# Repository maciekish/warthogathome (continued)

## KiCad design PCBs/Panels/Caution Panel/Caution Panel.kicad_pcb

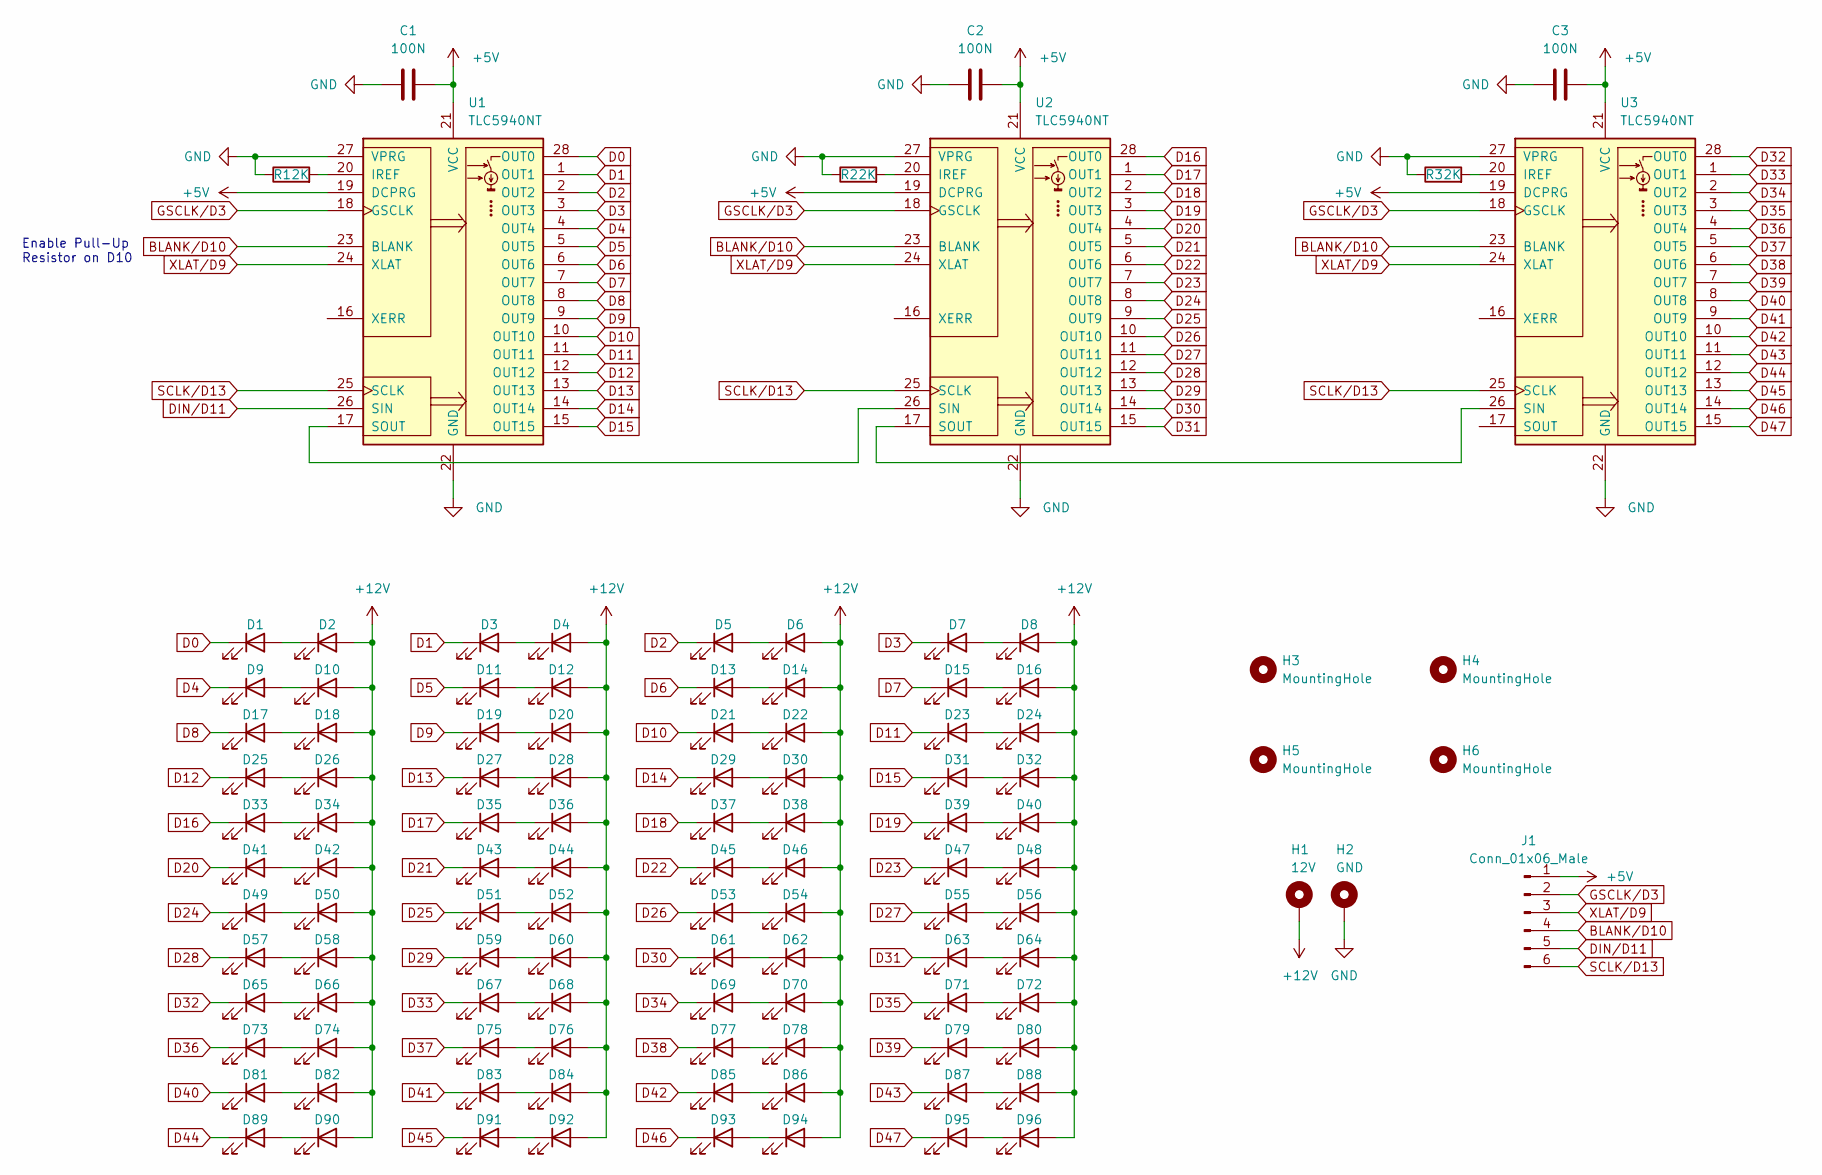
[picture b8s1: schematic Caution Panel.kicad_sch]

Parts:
C1, C2, C3: 100N; C_0805_2012Metric_Pad1.18x1.45mm_HandSolder
D1, D2, D3, D4, D5, D6, D7, D8, D9, D10, D11, D12, D13, D14, D15, D16, D17, D18, D19, D20, D21, D22, D23, D24, D25, D26, D27, D28, D29, D30, D31, D32, D33, D34, D35, D36, D37, D38, D39, D40, D41, D42, D43, D44, D45, D46, D47, D48, D49, D50, D51, D52, D53, D54, D55, D56, D57, D58, D59, D60, D61, D62, D63, D64, D65, D66, D67, D68, D69, D70, D71, D72, D73, D74, D75, D76, D77, D78, D79, D80, D81, D82, D83, D84, D85, D86, D87, D88, D89, D90, D91, D92, D93, D94, D95, D96: GREEN; LED_2010_5025Metric_Pad1.52x2.65mm_HandSolder
H1: 12V; MountingHole_2.2mm_M2_Pad
H2: GND; MountingHole_2.2mm_M2_Pad
H3, H4, H5, H6: MountingHole; MountingHole_4mm
J1: Conn_01x06_Male; PinHeader_1x06_P2.54mm_Vertical
R1, R2, R3: 2K; R_1210_3225Metric_Pad1.30x2.65mm_HandSolder
U1, U2, U3: TLC5940NT; DIP-28_W7.62mm

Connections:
+5V: C1.2, C2.2, C3.2, J1.1, U1.19 (DCPRG), U1.21 (VCC), U2.19 (DCPRG), U2.21 (VCC), U3.19 (DCPRG), U3.21 (VCC)
+12V: D2.2 (A), D4.2 (A), D6.2 (A), D8.2 (A), D10.2 (A), D12.2 (A), D14.2 (A), D16.2 (A), D18.2 (A), D20.2 (A), D22.2 (A), D24.2 (A), D26.2 (A), D28.2 (A), D30.2 (A), D32.2 (A), D34.2 (A), D36.2 (A), D38.2 (A), D40.2 (A), D42.2 (A), D44.2 (A), D46.2 (A), D48.2 (A), D50.2 (A), D52.2 (A), D54.2 (A), D56.2 (A), D58.2 (A), D60.2 (A), D62.2 (A), D64.2 (A), D66.2 (A), D68.2 (A), D70.2 (A), D72.2 (A), D74.2 (A), D76.2 (A), D78.2 (A), D80.2 (A), D82.2 (A), D84.2 (A), D86.2 (A), D88.2 (A), D90.2 (A), D92.2 (A), D94.2 (A), D96.2 (A), H1.1
BLANK/D10: J1.4, U1.23 (BLANK), U2.23 (BLANK), U3.23 (BLANK)
D0: D1.1 (K), U1.28 (OUT0)
D1: D3.1 (K), U1.1 (OUT1)
D2: D5.1 (K), U1.2 (OUT2)
D3: D7.1 (K), U1.3 (OUT3)
D4: D9.1 (K), U1.4 (OUT4)
D5: D11.1 (K), U1.5 (OUT5)
D6: D13.1 (K), U1.6 (OUT6)
D7: D15.1 (K), U1.7 (OUT7)
D8: D17.1 (K), U1.8 (OUT8)
D9: D19.1 (K), U1.9 (OUT9)
D10: D21.1 (K), U1.10 (OUT10)
D11: D23.1 (K), U1.11 (OUT11)
D12: D25.1 (K), U1.12 (OUT12)
D13: D27.1 (K), U1.13 (OUT13)
D14: D29.1 (K), U1.14 (OUT14)
D15: D31.1 (K), U1.15 (OUT15)
D16: D33.1 (K), U2.28 (OUT0)
D17: D35.1 (K), U2.1 (OUT1)
D18: D37.1 (K), U2.2 (OUT2)
D19: D39.1 (K), U2.3 (OUT3)
D20: D41.1 (K), U2.4 (OUT4)
D21: D43.1 (K), U2.5 (OUT5)
D22: D45.1 (K), U2.6 (OUT6)
D23: D47.1 (K), U2.7 (OUT7)
D24: D49.1 (K), U2.8 (OUT8)
D25: D51.1 (K), U2.9 (OUT9)
D26: D53.1 (K), U2.10 (OUT10)
D27: D55.1 (K), U2.11 (OUT11)
D28: D57.1 (K), U2.12 (OUT12)
D29: D59.1 (K), U2.13 (OUT13)
D30: D61.1 (K), U2.14 (OUT14)
D31: D63.1 (K), U2.15 (OUT15)
D32: D65.1 (K), U3.28 (OUT0)
D33: D67.1 (K), U3.1 (OUT1)
D34: D69.1 (K), U3.2 (OUT2)
D35: D71.1 (K), U3.3 (OUT3)
D36: D73.1 (K), U3.4 (OUT4)
D37: D75.1 (K), U3.5 (OUT5)
D38: D77.1 (K), U3.6 (OUT6)
D39: D79.1 (K), U3.7 (OUT7)
D40: D81.1 (K), U3.8 (OUT8)
D41: D83.1 (K), U3.9 (OUT9)
D42: D85.1 (K), U3.10 (OUT10)
D43: D87.1 (K), U3.11 (OUT11)
D44: D89.1 (K), U3.12 (OUT12)
D45: D91.1 (K), U3.13 (OUT13)
D46: D93.1 (K), U3.14 (OUT14)
D47: D95.1 (K), U3.15 (OUT15)
DIN/D11: J1.5, U1.26 (SIN)
GND: C1.1, C2.1, C3.1, H2.1, R1.1, R2.1, R3.1, U1.22 (GND), U1.27 (VPRG), U2.22 (GND), U2.27 (VPRG), U3.22 (GND), U3.27 (VPRG)
GSCLK/D3: J1.2, U1.18 (GSCLK), U2.18 (GSCLK), U3.18 (GSCLK)
unnamed: D1.2 (A), D2.1 (K)
unnamed: D3.2 (A), D4.1 (K)
unnamed: D5.2 (A), D6.1 (K)
unnamed: D7.2 (A), D8.1 (K)
unnamed: D9.2 (A), D10.1 (K)
unnamed: D11.2 (A), D12.1 (K)
unnamed: D13.2 (A), D14.1 (K)
unnamed: D15.2 (A), D16.1 (K)
unnamed: D17.2 (A), D18.1 (K)
unnamed: D19.2 (A), D20.1 (K)
unnamed: D21.2 (A), D22.1 (K)
unnamed: D23.2 (A), D24.1 (K)
unnamed: D25.2 (A), D26.1 (K)
unnamed: D27.2 (A), D28.1 (K)
unnamed: D29.2 (A), D30.1 (K)
unnamed: D31.2 (A), D32.1 (K)
unnamed: D33.2 (A), D34.1 (K)
unnamed: D35.2 (A), D36.1 (K)
unnamed: D37.2 (A), D38.1 (K)
unnamed: D39.2 (A), D40.1 (K)
unnamed: D41.2 (A), D42.1 (K)
unnamed: D43.2 (A), D44.1 (K)
unnamed: D45.2 (A), D46.1 (K)
unnamed: D47.2 (A), D48.1 (K)
unnamed: D49.2 (A), D50.1 (K)
unnamed: D51.2 (A), D52.1 (K)
unnamed: D53.2 (A), D54.1 (K)
unnamed: D55.2 (A), D56.1 (K)
unnamed: D57.2 (A), D58.1 (K)
unnamed: D59.2 (A), D60.1 (K)
unnamed: D61.2 (A), D62.1 (K)
unnamed: D63.2 (A), D64.1 (K)
unnamed: D65.2 (A), D66.1 (K)
unnamed: D67.2 (A), D68.1 (K)
unnamed: D69.2 (A), D70.1 (K)
unnamed: D71.2 (A), D72.1 (K)
unnamed: D73.2 (A), D74.1 (K)
unnamed: D75.2 (A), D76.1 (K)
unnamed: D77.2 (A), D78.1 (K)
unnamed: D79.2 (A), D80.1 (K)
unnamed: D81.2 (A), D82.1 (K)
unnamed: D83.2 (A), D84.1 (K)
unnamed: D85.2 (A), D86.1 (K)
unnamed: D87.2 (A), D88.1 (K)
unnamed: D89.2 (A), D90.1 (K)
unnamed: D91.2 (A), D92.1 (K)
unnamed: D93.2 (A), D94.1 (K)
unnamed: D95.2 (A), D96.1 (K)
unnamed: R1.2, U1.20 (IREF)
unnamed: R2.2, U2.20 (IREF)
unnamed: R3.2, U3.20 (IREF)
unnamed: U1.17 (SOUT), U2.26 (SIN)
unnamed: U2.17 (SOUT), U3.26 (SIN)
SCLK/D13: J1.6, U1.25 (SCLK), U2.25 (SCLK), U3.25 (SCLK)
XLAT/D9: J1.3, U1.24 (XLAT), U2.24 (XLAT), U3.24 (XLAT)

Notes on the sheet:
Enable Pull-Up Resistor on D10

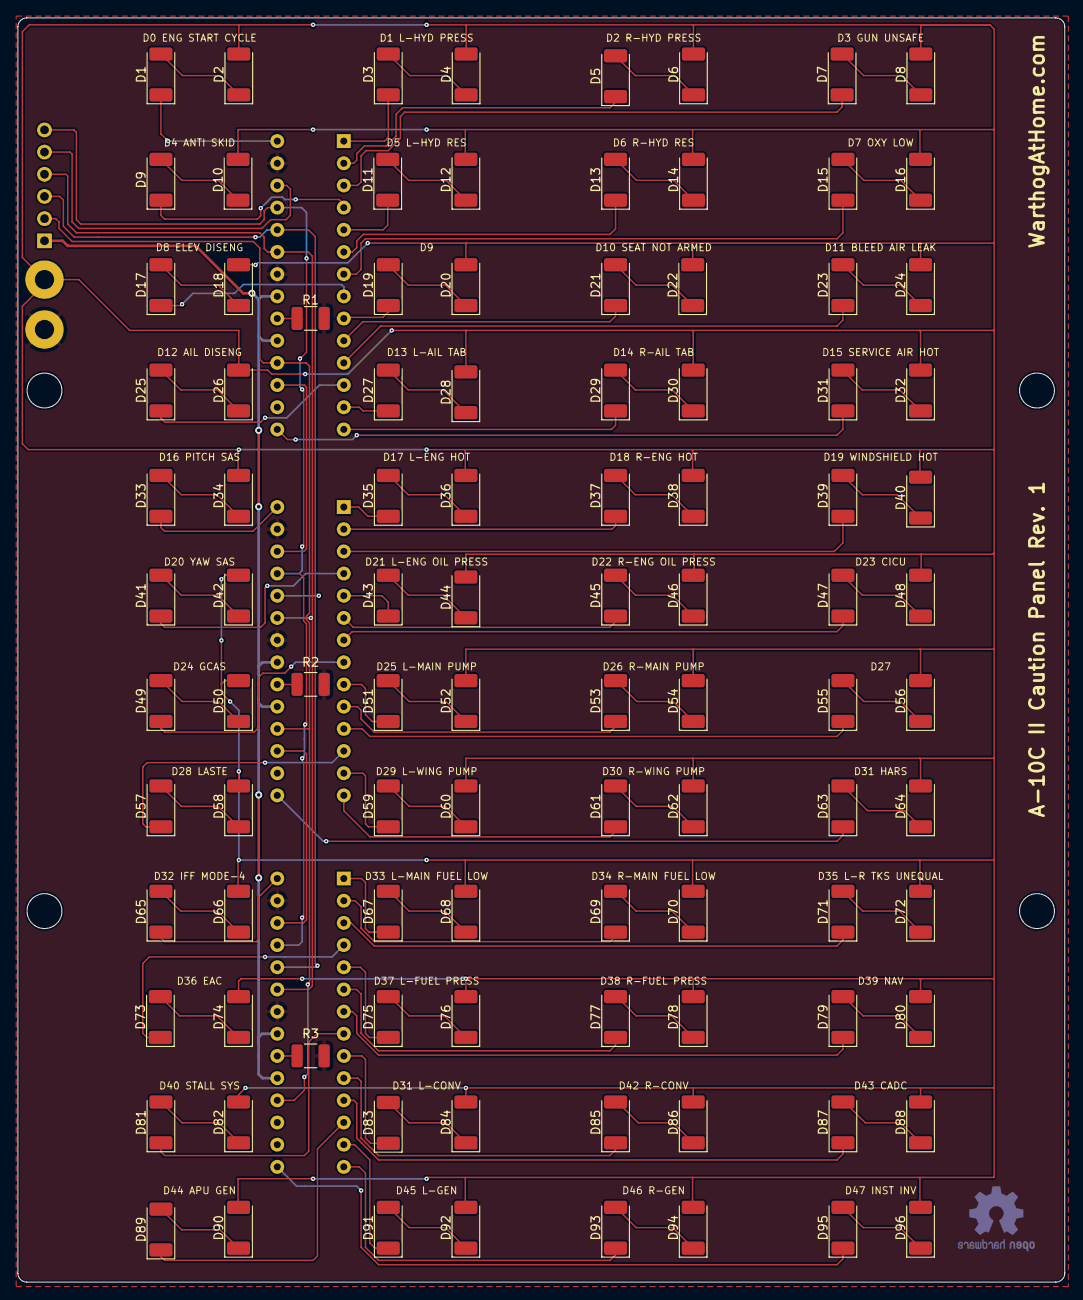
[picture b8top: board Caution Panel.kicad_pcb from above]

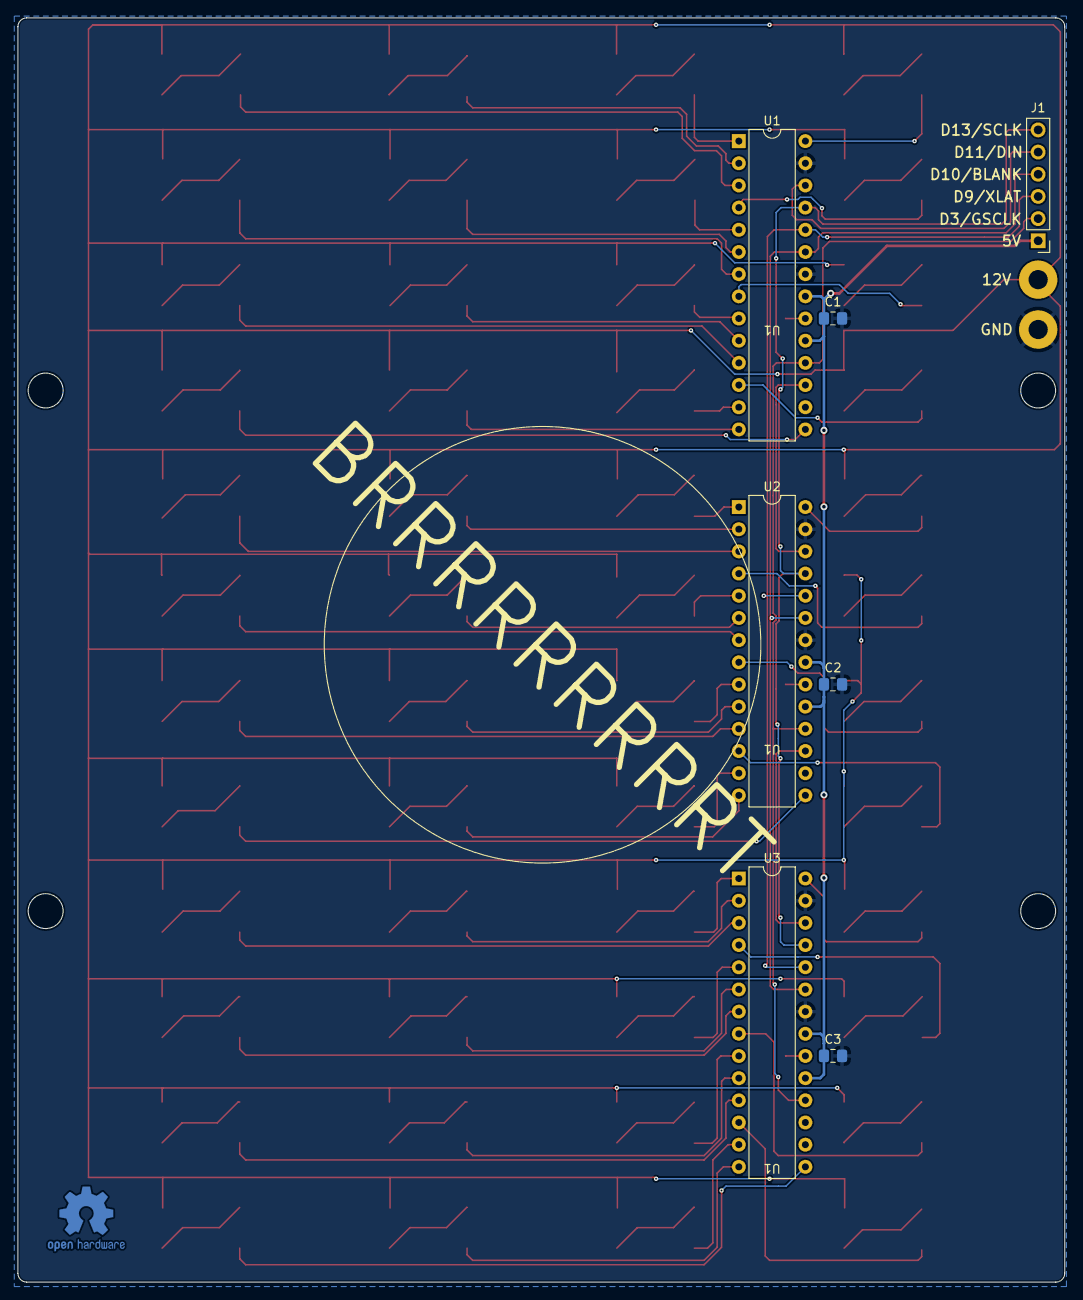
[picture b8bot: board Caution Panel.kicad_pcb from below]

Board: 2 copper layers, 119.9 x 144.8 mm, 112 parts (7 on the bottom side), 109 nets.

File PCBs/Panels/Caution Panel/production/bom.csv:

Designator,Footprint,Quantity,Value,LCSC Part #
D91,LED_2010_5025Metric_Pad1.52x2.65mm_HandSolder,1,GREEN,
D94,LED_2010_5025Metric_Pad1.52x2.65mm_HandSolder,1,GREEN,
D40,LED_2010_5025Metric_Pad1.52x2.65mm_HandSolder,1,GREEN,
D22,LED_2010_5025Metric_Pad1.52x2.65mm_HandSolder,1,GREEN,
D83,LED_2010_5025Metric_Pad1.52x2.65mm_HandSolder,1,GREEN,
D77,LED_2010_5025Metric_Pad1.52x2.65mm_HandSolder,1,GREEN,
R1,R_1210_3225Metric_Pad1.30x2.65mm_HandSolder,1,2K,
H2,MountingHole_2.2mm_M2_Pad,1,GND,
D86,LED_2010_5025Metric_Pad1.52x2.65mm_HandSolder,1,GREEN,
D95,LED_2010_5025Metric_Pad1.52x2.65mm_HandSolder,1,GREEN,
D37,LED_2010_5025Metric_Pad1.52x2.65mm_HandSolder,1,GREEN,
D75,LED_2010_5025Metric_Pad1.52x2.65mm_HandSolder,1,GREEN,
D78,LED_2010_5025Metric_Pad1.52x2.65mm_HandSolder,1,GREEN,
D12,LED_2010_5025Metric_Pad1.52x2.65mm_HandSolder,1,GREEN,
D65,LED_2010_5025Metric_Pad1.52x2.65mm_HandSolder,1,GREEN,
D67,LED_2010_5025Metric_Pad1.52x2.65mm_HandSolder,1,GREEN,
D68,LED_2010_5025Metric_Pad1.52x2.65mm_HandSolder,1,GREEN,
D6,LED_2010_5025Metric_Pad1.52x2.65mm_HandSolder,1,GREEN,
D72,LED_2010_5025Metric_Pad1.52x2.65mm_HandSolder,1,GREEN,
D17,LED_2010_5025Metric_Pad1.52x2.65mm_HandSolder,1,GREEN,
D23,LED_2010_5025Metric_Pad1.52x2.65mm_HandSolder,1,GREEN,
D51,LED_2010_5025Metric_Pad1.52x2.65mm_HandSolder,1,GREEN,
D89,LED_2010_5025Metric_Pad1.52x2.65mm_HandSolder,1,GREEN,
D35,LED_2010_5025Metric_Pad1.52x2.65mm_HandSolder,1,GREEN,
D31,LED_2010_5025Metric_Pad1.52x2.65mm_HandSolder,1,GREEN,
D55,LED_2010_5025Metric_Pad1.52x2.65mm_HandSolder,1,GREEN,
D7,LED_2010_5025Metric_Pad1.52x2.65mm_HandSolder,1,GREEN,
D69,LED_2010_5025Metric_Pad1.52x2.65mm_HandSolder,1,GREEN,
H5,MountingHole_4mm,1,MountingHole,
D2,LED_2010_5025Metric_Pad1.52x2.65mm_HandSolder,1,GREEN,
D73,LED_2010_5025Metric_Pad1.52x2.65mm_HandSolder,1,GREEN,
D11,LED_2010_5025Metric_Pad1.52x2.65mm_HandSolder,1,GREEN,
D27,LED_2010_5025Metric_Pad1.52x2.65mm_HandSolder,1,GREEN,
D71,LED_2010_5025Metric_Pad1.52x2.65mm_HandSolder,1,GREEN,
D84,LED_2010_5025Metric_Pad1.52x2.65mm_HandSolder,1,GREEN,
D45,LED_2010_5025Metric_Pad1.52x2.65mm_HandSolder,1,GREEN,
D15,LED_2010_5025Metric_Pad1.52x2.65mm_HandSolder,1,GREEN,
D30,LED_2010_5025Metric_Pad1.52x2.65mm_HandSolder,1,GREEN,
D57,LED_2010_5025Metric_Pad1.52x2.65mm_HandSolder,1,GREEN,
D13,LED_2010_5025Metric_Pad1.52x2.65mm_HandSolder,1,GREEN,
D56,LED_2010_5025Metric_Pad1.52x2.65mm_HandSolder,1,GREEN,
D59,LED_2010_5025Metric_Pad1.52x2.65mm_HandSolder,1,GREEN,
D92,LED_2010_5025Metric_Pad1.52x2.65mm_HandSolder,1,GREEN,
D44,LED_2010_5025Metric_Pad1.52x2.65mm_HandSolder,1,GREEN,
D79,LED_2010_5025Metric_Pad1.52x2.65mm_HandSolder,1,GREEN,
D26,LED_2010_5025Metric_Pad1.52x2.65mm_HandSolder,1,GREEN,
H4,MountingHole_4mm,1,MountingHole,
D63,LED_2010_5025Metric_Pad1.52x2.65mm_HandSolder,1,GREEN,
D20,LED_2010_5025Metric_Pad1.52x2.65mm_HandSolder,1,GREEN,
D43,LED_2010_5025Metric_Pad1.52x2.65mm_HandSolder,1,GREEN,
D34,LED_2010_5025Metric_Pad1.52x2.65mm_HandSolder,1,GREEN,
D4,LED_2010_5025Metric_Pad1.52x2.65mm_HandSolder,1,GREEN,
D46,LED_2010_5025Metric_Pad1.52x2.65mm_HandSolder,1,GREEN,
H3,MountingHole_4mm,1,MountingHole,
D38,LED_2010_5025Metric_Pad1.52x2.65mm_HandSolder,1,GREEN,
R3,R_1210_3225Metric_Pad1.30x2.65mm_HandSolder,1,2K,
D21,LED_2010_5025Metric_Pad1.52x2.65mm_HandSolder,1,GREEN,
D49,LED_2010_5025Metric_Pad1.52x2.65mm_HandSolder,1,GREEN,
D36,LED_2010_5025Metric_Pad1.52x2.65mm_HandSolder,1,GREEN,
D1,LED_2010_5025Metric_Pad1.52x2.65mm_HandSolder,1,GREEN,
D18,LED_2010_5025Metric_Pad1.52x2.65mm_HandSolder,1,GREEN,
D14,LED_2010_5025Metric_Pad1.52x2.65mm_HandSolder,1,GREEN,
D81,LED_2010_5025Metric_Pad1.52x2.65mm_HandSolder,1,GREEN,
D70,LED_2010_5025Metric_Pad1.52x2.65mm_HandSolder,1,GREEN,
H1,MountingHole_2.2mm_M2_Pad,1,12V,
D10,LED_2010_5025Metric_Pad1.52x2.65mm_HandSolder,1,GREEN,
D42,LED_2010_5025Metric_Pad1.52x2.65mm_HandSolder,1,GREEN,
D32,LED_2010_5025Metric_Pad1.52x2.65mm_HandSolder,1,GREEN,
H6,MountingHole_4mm,1,MountingHole,
D80,LED_2010_5025Metric_Pad1.52x2.65mm_HandSolder,1,GREEN,
D48,LED_2010_5025Metric_Pad1.52x2.65mm_HandSolder,1,GREEN,
D16,LED_2010_5025Metric_Pad1.52x2.65mm_HandSolder,1,GREEN,
D62,LED_2010_5025Metric_Pad1.52x2.65mm_HandSolder,1,GREEN,
D25,LED_2010_5025Metric_Pad1.52x2.65mm_HandSolder,1,GREEN,
D3,LED_2010_5025Metric_Pad1.52x2.65mm_HandSolder,1,GREEN,
D47,LED_2010_5025Metric_Pad1.52x2.65mm_HandSolder,1,GREEN,
R2,R_1210_3225Metric_Pad1.30x2.65mm_HandSolder,1,2K,
D8,LED_2010_5025Metric_Pad1.52x2.65mm_HandSolder,1,GREEN,
D90,LED_2010_5025Metric_Pad1.52x2.65mm_HandSolder,1,GREEN,
D19,LED_2010_5025Metric_Pad1.52x2.65mm_HandSolder,1,GREEN,
D41,LED_2010_5025Metric_Pad1.52x2.65mm_HandSolder,1,GREEN,
D76,LED_2010_5025Metric_Pad1.52x2.65mm_HandSolder,1,GREEN,
D61,LED_2010_5025Metric_Pad1.52x2.65mm_HandSolder,1,GREEN,
D58,LED_2010_5025Metric_Pad1.52x2.65mm_HandSolder,1,GREEN,
D74,LED_2010_5025Metric_Pad1.52x2.65mm_HandSolder,1,GREEN,
D9,LED_2010_5025Metric_Pad1.52x2.65mm_HandSolder,1,GREEN,
D5,LED_2010_5025Metric_Pad1.52x2.65mm_HandSolder,1,GREEN,
D54,LED_2010_5025Metric_Pad1.52x2.65mm_HandSolder,1,GREEN,
D24,LED_2010_5025Metric_Pad1.52x2.65mm_HandSolder,1,GREEN,
D29,LED_2010_5025Metric_Pad1.52x2.65mm_HandSolder,1,GREEN,
D50,LED_2010_5025Metric_Pad1.52x2.65mm_HandSolder,1,GREEN,
D60,LED_2010_5025Metric_Pad1.52x2.65mm_HandSolder,1,GREEN,
D64,LED_2010_5025Metric_Pad1.52x2.65mm_HandSolder,1,GREEN,
D28,LED_2010_5025Metric_Pad1.52x2.65mm_HandSolder,1,GREEN,
D87,LED_2010_5025Metric_Pad1.52x2.65mm_HandSolder,1,GREEN,
D39,LED_2010_5025Metric_Pad1.52x2.65mm_HandSolder,1,GREEN,
D88,LED_2010_5025Metric_Pad1.52x2.65mm_HandSolder,1,GREEN,
D33,LED_2010_5025Metric_Pad1.52x2.65mm_HandSolder,1,GREEN,
D96,LED_2010_5025Metric_Pad1.52x2.65mm_HandSolder,1,GREEN,
D85,LED_2010_5025Metric_Pad1.52x2.65mm_HandSolder,1,GREEN,
D82,LED_2010_5025Metric_Pad1.52x2.65mm_HandSolder,1,GREEN,
D93,LED_2010_5025Metric_Pad1.52x2.65mm_HandSolder,1,GREEN,
D53,LED_2010_5025Metric_Pad1.52x2.65mm_HandSolder,1,GREEN,
D52,LED_2010_5025Metric_Pad1.52x2.65mm_HandSolder,1,GREEN,
D66,LED_2010_5025Metric_Pad1.52x2.65mm_HandSolder,1,GREEN,
U2,DIP-28_W7.62mm,1,TLC5940NT,
U1,DIP-28_W7.62mm,1,TLC5940NT,
U3,DIP-28_W7.62mm,1,TLC5940NT,
C3,C_0805_2012Metric_Pad1.18x1.45mm_HandSolder,1,100N,
J1,PinHeader_1x06_P2.54mm_Vertical,1,Conn_01x06_Male,
C1,C_0805_2012Metric_Pad1.18x1.45mm_HandSolder,1,100N,
C2,C_0805_2012Metric_Pad1.18x1.45mm_HandSolder,1,100N,

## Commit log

2022-08-02 Minor PCB adjustments
2022-08-02 Modified some panels for LED strips
2022-08-03 Added a 5v bus to all PCBs
2022-08-05 Create VHF_I2C.ino
    Added a VHF OLED test sketch
2022-08-05 Updated poster
2022-08-08 Migrated Master PCB to KiCad
2022-08-08 Fixed mounting holes Added Mega pin labels
2022-08-08 Added a ground pour to top layer
2022-08-09 Modified mounting holes to M3
2022-08-09 Added Micro Blade fuse holder to each bus Updated cap 3d model Ignored KiCad backups
2022-08-09 Fixed library search paths
2022-08-11 Fixed 3d model
2022-08-11 Added power status LEDs to Master PCB
2022-08-11 Added power status LED to each bus
2022-08-11 DRC Excludions
2022-08-15 Master PCB Adjustments
2022-08-15 Updated Master PCB and completed first version of Hub
2022-08-16 Completed first version of Master Shield
2022-08-17 JLCPCB mappings wip
2022-08-17 Final Master Shield files
2022-08-17 Fixed J1 silkscreen
2022-08-17 Added RJ45 to lib
2022-08-18 Cleaned up libraries
2022-08-18 Fixed Master Shield 3D model paths
2022-08-18 Updated LCSC number for fuse
2022-08-18 First version of Hub completed
2022-08-18 Added some more silkscreen info to Hub
2022-08-18 Updated libraries for Arduino components
2022-08-19 Updated HUB LEDs
2022-08-19 Initial Slave Schematic
2022-08-19 Annotated Slave
2022-08-19 Added LED terminals
2022-08-19 Replaced 4P switch with 2x2P switches because of placement
2022-08-20 Slave PCB wip
2022-08-23 Slave WIP
2022-08-28 Tweaked Hub
2022-08-28 Generated Final Rev 1 files for Hub and Slave
2022-08-28 Fixed swapped LEDs on Slave
2022-08-28 Updated production files for Slave
2022-08-28 Updated TX/RX resistors to 1.8K
2022-08-28 Removed unnecessary resistor
2022-08-28 Include headers in BOM
2022-08-28 Added Mounting Holes to Slave PCB Added External Connection PCB
2022-08-29 Updated External Connectors BOM
2022-08-29 Updated .gitignore
2022-08-29 Remove ignored files
2022-08-29 Renamed Slave to Nano Slave
2022-08-29 Removed Eagle Libraries and Projects
2022-08-29 Mega Slave WIP
2022-08-31 4wire SPI OLED example
2022-08-31 Updated OLED SPI example to use hardware SPI on Arduino Nano
2022-09-01 Updated SPI example with hardware SPI for Arduino Mega
2022-09-01 Added switch to KiCad library
2022-09-02 Custom fonts for CMSP
2022-09-02 Improved CMSP font and drawing
2022-09-02 Added comment
2022-09-02 First 3.5" TFT Example
2022-09-04 Updated TFT display example
2022-09-04 TFT Example
2022-09-04 Updated TXT Example
2022-09-04 Completed CDU TFT Example
2022-09-07 Mega Slave Initial Routing
2022-09-07 Mega Slave Completed
2022-09-08 Initial version of the Nano Shield
2022-09-08 Finished Nano Shield
2022-09-11 Nano Slave Rev 2
2022-09-11 Modified Courtyard
2022-09-11 Mega Shield WIP
2022-09-11 Updated some silkscreen
2022-09-11 Added measurements to silkscreen
2022-09-11 Fixed PCB size
2022-09-12 Cleaned up routing on Nano Shield
2022-09-13 Added backlight control to TFT via hardware mod
2022-09-13 First version of ELEC PWR sketch
2022-09-19 Rearranged files
2022-09-19 Mega Slave Rev. 2 Completed
2022-09-22 Code cleanup
2022-09-22 Completed panels for right column of right console
2022-10-01 Completed Caution Panel
2022-10-04 UFC WIP
2022-10-10 Added Laser Calibration Files
2022-10-10 UFC Completed
2022-10-12 Updated PCB production files
2022-10-13 Fixed part number of screw terminals
2022-10-19 Use 1/4 duty cycle for backlight
2022-11-03 Nano SFF Slave
2022-11-07 Cleaned up PCB
2022-11-07 Mega SFF Slave WIP
2022-11-11 Mega SFF WIP
2022-11-12 Mega SFF Slave Rev. 1
2022-11-12 Nano SFF Rev. 1
2022-11-14 Misc files
2022-12-01 Updated production files
2022-12-01 3D Models & Oxygen Regulator code WIP
2022-12-01 Fixed terminal part number
2022-12-01 Fixed silkscreen
2022-12-04 Updated Nano SFF Slave RS485 Switch and Silkscreen
2022-12-04 Updated Mega SFF Slave RS485 Switch and Silkscreen
2022-12-04 Improved Nano SFF Silkscreen
2022-12-05 Added fuse models
2022-12-05 Micro SFF Slave WIP
2022-12-09 Simulation
2022-12-09 Nano SFF with DS4560S-AR+ hotplug protection (Not Orderable)
2022-12-09 Added a drain resistor and updated component values
2022-12-09 Added new components
2022-12-15 Nano SFF With Hotplug and RS485 Protection
2022-12-15 Added Hotplug and RS485 protection to Mega SFF Schematic. PCB to go
2022-12-15 Fixed silkscreen on Nano SFF
2022-12-15 Added Hotplug and RS485 protection to Mega SFF. Capacitor LCSC numbers to go.
2022-12-15 Updated LCSC number and size of voltage ramp capacitors for Nano SFF Slave
2022-12-15 Updated LCSC number and size of voltage ramp capacitors for Mega SFF Slave
2022-12-16 Added Caution Panel and panelized 3 panels for production
2022-12-16 Added a top cover for the Caution Panel
2022-12-16 Added checklists
2022-12-16 Added more checklists
2022-12-19 Oxygen Regulator Sketch
2022-12-21 Updated panelized files
2022-12-26 Updated micro-fit pinout for more power
2022-12-26 Updated hub pinout for more power
2022-12-29 Updated Nano SFF Slave for correct block terminal size
2022-12-29 Regenerated production files
2022-12-29 Updated Mega SFF Slave for correct terminal block size
2022-12-29 Updated Nano SFF Revision and date information
2022-12-31 Master WIP
2023-01-01 Added 1 pos dip switch
2023-01-02 Master Rev. 1
2023-01-02 Updated Master Silkscreen
2023-01-02 Tweaked Groundplane Size
2023-01-03 Updated Master to use PCIe Power Directly
2023-01-03 Added Spring Terminals
2023-01-09 Updated HUB
2023-01-09 Removed voltage ramp and some protection from Nano SFF Slave
2023-01-09 Updated Nano SFF Slave
2023-01-11 Arduino Code for Lighting Panel
